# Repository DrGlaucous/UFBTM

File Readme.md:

# UFBTM
~~*Unnamed Full Body Tracking modules*~~

*They have a name now...*
# Mr. Tracker
A cheap, compact, and open-source realtime tracking module built with slimeVR and the ESP32.

<div style="display: flex;">

</div>

## Design goal
<details open>
<summary>
    Details
</summary>

The components for these trackers have been chosen to be **exclusively through-hole** for ease of assembly (at a slight cost of a larger size)

The main IMU this design is based around is the BMI160, primarily for its low cost and small breakout footprint. This IMU is notorious for drifting, so it is also paired with a GY-271 magnetometer to mitigate some of the drift (depending on use location, the magnetometers may need to be disabled due to poor magnetic field).

<figure align = "center">

</figure>

This idea is by no means novel; I'm not even the first person to use the components I'm using, but I'm attempting to take a cost approach here. The full tracking set (10 modules + 5 extenders) can potentially be as low as $100 USD without print time costs or filament prices.

Assembly should be quick and reliable with no need for SMD or rework, which is something other modules of this size can't do.

The module uses TRRS (4 ring) aux jacks to connect between the main board and its extender, providing a robust connection that can last many plug cycles and be easily replaced if the wire goes bad.

Battery life of these trackers should be comparable to official ESP8266-based slime trackers, though I've only personally used them for about 6-8 hours at a time.

</details>

## Compatibility

<details>
<summary>
    MCU
</summary>

### MCU
For the microcontroller, this board can support anything with the "superMini" form factor with the 8 or 9 pin length (including the s3 variants, though I haven't tested the firmware with the s3)

<div class="image-row" style="display:flex;flex-wrap:wrap">
    <div class="image-col" style="flex:50%">
        <div class="grid-item">
            
        </div>
    </div>
    <div class="image-col" style="flex:50%">
        <div class="grid-item">
            
        </div>
    </div>
</div>

> [!NOTE]
> ***Check to make sure the +5v, GND, and +3.3v on the board match the "standard" superMini layout as seen above! Some boards like to mix them around, like the one below. That one WILL NOT WORK.***

<figure align = "center">

<figcaption align = "center"><i>Note how the power pins are on the opposite side from the normal superMini board</i></figcaption>
</figure>

---
My preference is the variant commonly labeled as "Pro Minis" or "C3 Minis" because [the normal "Supermini" modules can have issues with antenna reception](https://peterneufeld.wordpress.com/2025/03/04/esp32-c3-supermini-antenna-modification/), depending on which ones you get. *(and it's a mixed bag, so you're never really sure if you're getting the right ones)*

The "Pro Mini" modules have a larger antenna that seems further spaced from the rest of the components. They're distinct enough that you always know you're getting the right type of board, and as far as I can tell, haven't been complained about online. They also have a place for an external antenna, should you ever want to go that route. SuperMini v2 modules also work well, but are typically more expensive.

<figure align = "center">

<figcaption align = "center"><i>An example of an "ESP32 C3 pro mini"</i></figcaption>
</figure>

</details>

---

<details>
<summary>
    IMU
</summary>

### IMU
The IMU can be anything that matches the BMI160 breakout form-factor.
This includes:
- The BMI160 itself
- The LSM6DS3 (*note: getting these from AliExpress will often just get you a re-badged BMI160.*) These aren't officially supported by the upstream slimeVR firmware as-of-writing, but are supported by my custom fork.
- Slimevr "Mumo" boards hosting a CM-45686 module
- [Mofflab](https://moffshop.deyta.de/products/lsm6dsv-module) LSM6DSV modules *(I'm sure there are other vendors of these that I haven't mentioned, but these are all I could find while searching the internet. Join the SVR discord if you want to find better sources)*

<div class="image-row" style="display:flex;flex-wrap:wrap">
    <div class="image-col" style="flex:50%">
        <div class="grid-item">
            
        </div>
        <div class="grid-item">
            
        </div>
    </div>
    <div class="image-col" style="flex:50%">
        <div class="grid-item">
            
        </div>
        <div class="grid-item">
            
        </div>
    </div>
</div>

</details>

---

<details>
<summary>
    Magnetometer
</summary>

### Magnetometer

The PCB was designed to hold a GY-271 magnetometer breakout board.
These boards are common enough, but tend to have several variants of actual magnetometer on them, including:
- HMC5883L
- QMC5883L
- QMC5883P

All these are supported by my fork of the slimeVR firmware *(with the BMI160 and LSM6DS3, I haven't tested with the mumos or mofflab boards, but if the IMU on those are good enough, you shouldn't need a magnetometer anyway)*, but they have distinct registers, so you will have to check which one you have. (as-of-writing, the QMC5883P is the most common of these)

<figure align = "center">

</figure>

</details>

---

<details>
<summary>
    Charger
</summary>

### Charger

One of the most compact jellybean chargers are the `LX-LBES` chargers. They tend to come in 2 distinct sizes, and it's unreliable which one you might get. The PCB can support either of them though, so this shouldn't be a problem. These are also commonly labeled as `TP4057` charger boards.

Just make sure it's the `LX-LBES` module and not the other variants like the `LX-MILC` or `LX-LBC3`, both of which are similarly sized, but are incompatible.

<figure align = "center">
<div class="image-row" style="display:flex;flex-wrap:wrap">
    <div class="image-col" style="flex:50%">
        <div class="grid-item">
            
        </div>
    </div>
    <div class="image-col" style="flex:50%">
        <div class="grid-item">
            
        </div>
    </div>
</div>
<figcaption align = "center"><i>On the left: the smaller of the two LX-LBES boards, on the right: the more common larger variant. Both of these will work for these trackers</i></figcaption>
</figure>

<figure align = "center">

</figure>

</details>

---

<details>
<summary>
    Battery
</summary>

### Battery

This tracker is designed to work with 2 distinct battery sizes:
- The 804040 (a square flat-pack, used with Mr. Tracker PCBs)
- The 18650 (a common cylindrical battery, used with Mrs. Tracker PCBs)

Unfortunately, I have not modeled a housing for the 18650 variant yet.

18650 batteries are cheaper than the 804040s, especially if you get them used from a place like [batteryhookup](https://batteryhookup.com/), where they cost about 50c per battery. Depending on the quality of the cell, they can also hold more charge than the 804040s, but as a trade-off are inconveniently shaped for trackers. The Mrs. Tracker PCB is designed to accommodate these long, skinny batteries as best as possible.

<figure align = "center">

</figure>

</details>

---

<details>
<summary>
    LDO
</summary>

### LDO

The LDO regulates the incoming battery voltage down to 3.3 volts for the electronics. The board will accept any LDO in a TO-92 package, but was designed around the HT7333 regulator as that is what I could get off Amazon.

If the LDO you select has a different pinout than the HT7333, then you will need to reconfigure the jumpers as described in [Power configuration](#power-configuration).

<figure align = "center">

</figure>

This part is optional if your IMU has a built-in 5v to 3.3v regulator **that can support the currents required by the ESP32 and other componets**. I've seen some that both could and couldn't, so I'd assume the worst case and use a discrete LDO for safety.

The MCP1700 also shares the same pinout and is rated at 250mA.

#### Capacitor requirements
Many of these LDOs require an inline capacitor for voltage smoothing and stable output (for example, the datasheet for the MCP1700 regulator says it requires at least a 1uf capacitor). I was able to find 10uf ceramic capacitors to use in my design, but you may be able to get away with smaller values, or even none at all. The HT7333 worked without a capacitor too, but it would have trouble slightly sooner than with a capacitor when the battery voltage got too low.

</details>

## Bill of Materials

Prices are generally cheaper if you buy in bulk from China, which is recommended since you'll likely be building at least five of these and need to order the PCBs from there anyway. (unless you *have* to use a domestic PCB manufacturer, in which case you'll probably end up paying several times more than ordering through a provider like JLCPCB)
Most of this stuff should be available to get on Amazon as well, albeit more expensive.

I've added some links to the BOMs below to help new builders get started, but there might be better deals for the same parts with some shopping around, which I encourage you to do.

> [!NOTE]
> ***Some of the links below have multiple options on the listing (like the resistors for instance. Make sure you choose the correct type!)***

### Mr/Mrs. Tracker part list
---
|part|qty per tracker|qty per package (typical)|price per package (typical, USD)|Link (non-affiliate, U.S. domain, may be expired)|
|-|-|-|-|-|
|PCB (ordered from PCB provider)|1|5-20|~$10 excluding shipping|[JLCPCB](https://jlcpcb.com/)|
|ESP32 C3 [(see compatible devices)](#mcu)|1|1|~$2.5|[AliExpress](https://www.aliexpress.us/item/3256808596276264.html)
|IMU [(see compatible devices)](#imu)|1|1|~$2.5|[AliExpress](https://www.aliexpress.us/item/3256806936640318.html)
|GY-271 Magnetometer [(see compatible devices)](#magnetometer) *(optional, but recommended to limit drift)*|1|1|~$2|[AliExpress](https://www.aliexpress.us/item/3256808812894856.html)
|LX-LBES li-ion charger [(see compatible devices)](#charger)|1|5-10|~$5|[AliExpress](https://www.aliexpress.us/item/3256807364882965.html)
|3.3v LDO [(see compatible devices)](#ldo)|1|20-100|~$3|[AliExpress](https://www.aliexpress.us/item/3256807332164741.html)
|10uF Ceramic Capacitor [(maybe optional, see LDO)](#capacitor-requirements)|1|100|~$3|[AliExpress](https://www.aliexpress.us/item/3256809085304078.html)
|200K resistor (for voltmeter)|2|100|~$2|[AliExpress](https://www.aliexpress.us/item/3256802310109990.html)
|On-Off Switch (SK12D07VG4)|1|100|~$2|[AliExpress](https://www.aliexpress.us/item/2251832696379644.html)
|TRRS Connector (PJ-320A) *(Optional, for extenders)*|1|20|~$2|[AliExpress](https://www.aliexpress.us/item/2255800974971563.html)
|M2.5x6 self tapping screws|5|50|~$2|[AliExpress](https://www.aliexpress.us/item/3256805374708201.html), [Amazon](https://a.co/d/0iR6Q6Wc)
|804040 battery|1|5|~$18 USD|[AliExpress](https://www.aliexpress.us/item/3256806179780660.html)
|Elastic straps, 25mm wide|Varies|5 Meters|~$4|[AliExpress](https://www.aliexpress.us/item/2251832835409359.html)
|Strap Buckles, 25mm wide|1|5|~$5|[AliExpress](https://www.aliexpress.us/item/3256805860301514.html)
|Sewing thread for attaching buckles to straps|Varies|Varies|N.A.|N.A.
|Plastic housing|1|N.A.|N.A.|N.A.

### Extender (Tracker Jr) part list
---

|part|qty per tracker|qty per package (typical)|price per package (typical, USD)|Link (non-affiliate, U.S. domain, may be expired)|
|-|-|-|-|-|
|PCB (ordered from PCB provider)|1|5-20|~$10 excluding shipping|[JLCPCB](https://jlcpcb.com/)|
|IMU [(see compatible devices)](#imu)|1|1|~$2.5|[AliExpress](https://www.aliexpress.us/item/3256806936640318.html)
|GY-271 Magnetometer [(see compatible devices)](#magnetometer) *(optional, but recommended to limit drift)*|1|1|~$2|[AliExpress](https://www.aliexpress.us/item/3256808812894856.html)
|TRRS Connector (PJ-320A)|1|20|$2|[AliExpress](https://www.aliexpress.us/item/2255800974971563.html)
|TRRS Male-Male Aux cable, 1 meter|1|1|$2|[AliExpress](https://www.aliexpress.us/item/3256805991501373.html)
|Elastic straps, 25mm wide|Varies|5 Meters|$4|[AliExpress](https://www.aliexpress.us/item/2251832835409359.html)
|Strap Buckles, 25mm wide|1|5|~$5|[AliExpress](https://www.aliexpress.us/item/3256805860301514.html)
|Sewing thread for attaching buckles to straps|Varies|Varies|N.A.|N.A.
|Plastic housing|1|N.A.|N.A.|N.A.

## Power configuration

<details>
<summary>
    Details
</summary>

Rev. 3 boards have several jumpers on the underside that changes how the device can be powered so a wider range of parts can be used.

Depending on the quality of the IMU breakout board, the linear regulator and voltage smoothing capacitor may not be needed. This varies more than you'd think with distributors though, so it's not always safe to count on it. Additionally, some versions of the IMU breakout might not even have an integrated regulator at all, making the discrete regulator required.

- Jumpers `A`, `B`, `C`, and `D` alter the pinout for the voltage regulator and allow one with any pin arrangement to be installed.
- Connecting jumper `E` allows the board to use the voltage regulator on the IMU instead of the discrete one.
- Connecting jumper `F` allows the ESP32's USB port to charge the battery. The drawback is that charging the tracker will *always* turn on the ESP32, wasting power and charging slower.

The following is a table of all the possible voltage regulator pinouts and their corresponding jumper configs. An "O" means to leave the jumper at default (bridging positions 1 and 2), an "X" means to cut the jumper and flip it (bridging positions 2 and 3). "Flip" means to solder the regulator into the socket backwards 

>[!NOTE]
> Although I tried to keep the ABCD jumpers next to each other, their orientations are flipped! Pay close mind to what side of the jumper pad the "1" and "3" are on in the silkscreen!

|Pinout|A|B|C|D|Flip|
|-|-|-|-|-|-|
||O|O|O|O|O|
||O|O|X|X|O|
||X|X|O|O|O|
||X|X|O|O|X|
||O|O|X|X|X|
||O|O|O|O|X|

In a nutshell,
- AB flip 1 and 2,
- CD flip 2 and 3

</details>

---

> [!CAUTION]
> Everything below this point is very unfinished (as opposed to only slightly unfinished, as is seen above)

## Ordering PCBs

todo: this

## Recommended tools for assembly

In theory, these trackers can be assembled just fine with a [Wal-Mart special](https://www.walmart.com/ip/EverStart-Soldering-Iron-Model-5133-Red-120V-30W-Automotive-Electrical-Tool-New/744820237) *(link included for meme purposes only!)* soldering iron, a pair of children's safety scissors, a manicure file, and a sewing needle. Will you have a good time doing it? No, but it's definitely possible.

Instead of that, here's the list of tools I recommend to make assembly of these go smoothly:

- A Soldering Iron (the Wal-Mart special will work, but I suggest getting something at least partway decent on Amazon; good soldering irons can be had for less than $30.)
- Solder (lead solder is easier to work with, but lead-free works OK too if you're cautious about working with lead.)
- Flush cutters
- A needle file set (optional)
- SMD Tweezers
- Helping hands vice (optional)
- Small phillips screwdriver (for the screws on the housing)

For the straps:
- A pair of scissors (preferably not child safety ones)
- A lighter
- A sewing needle or sewing machine
- Sewing thread

## Assembly Preface

These guides assume you have everything in hand required to build one of these trackers.

Typically, a good rule of thumb is to start with the lowest profile components first and work your way up by height. Most of the stuff on these trackers is the same height however, so order isn't ultra-important; nothing really gets in the way of anything else, but regardless, I still like to start with the breakout boards *(MCU, IMU, Magnetometer, and Charger)*.

To keep the tracker as compact as possible, the breakouts are soldered directly on top of the board. This makes them much more difficult to remove though, so be careful during assembly!

I've had an IMU come to me dead on arrival and had to go through the painstaking process of desoldering it from the board. (which involved simultaneously heating the pins and wedging an xacto between the IMU and the PCB)
Because of that, I like to make sure that parts work beforehand by soldering up a test rig with removable pins to test parts with.

Working with a breadboard for testing is feasible too, but it's less likely that people would just have one of those onhand, much less the desire to wire an entire setup just to see if a few parts maybe don't work.

## Assembly (Mr. Tracker)

<details>
<summary>
    Details
</summary>

</details>

## Assembly (Mrs. Tracker)

## Assembly (Tracker Jr)

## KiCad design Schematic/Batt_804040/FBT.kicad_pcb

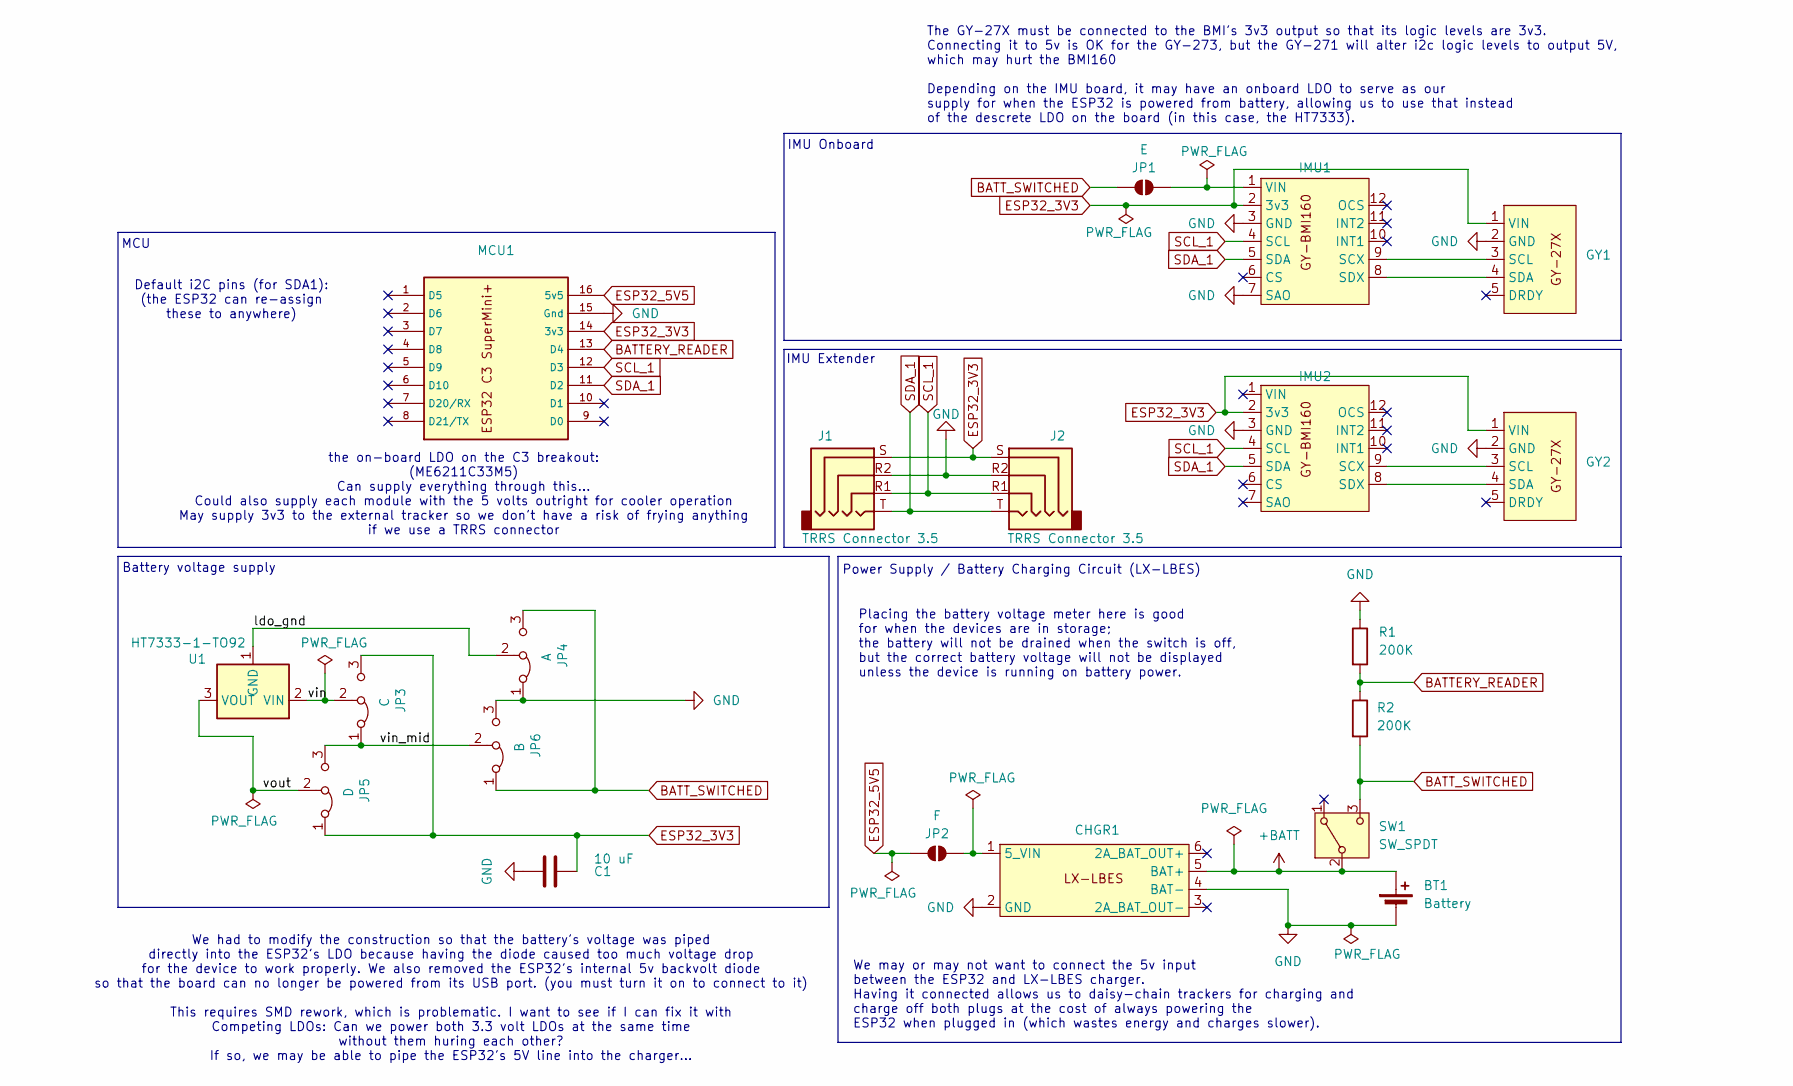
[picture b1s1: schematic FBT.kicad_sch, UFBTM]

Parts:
BT1: Battery; JST_XH_B2B-XH-A_1x02_P2.50mm_Vertical
C1: 10 uF; C_Disc_D5.0mm_W2.5mm_P5.00mm
CHGR1: LX_LBES
GY1, GY2: GY-271
IMU1, IMU2: GY-BMI160
J1, J2: TRRS Connector 3.5; PJ-320A
JP1: E; SolderJumper-2_P1.3mm_Open_RoundedPad1.0x1.5mm
JP2: F; SolderJumper-2_P1.3mm_Open_RoundedPad1.0x1.5mm
JP3: C; SolderJumper-3_P1.3mm_Bridged12_RoundedPad1.0x1.5mm_NumberL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
JP4: A; SolderJumper-3_P1.3mm_Bridged12_RoundedPad1.0x1.5mm_NumberL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
JP5: D; SolderJumper-3_P1.3mm_Bridged12_RoundedPad1.0x1.5mm_NumberL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
JP6: B; SolderJumper-3_P1.3mm_Bridged12_RoundedPad1.0x1.5mm_NumberL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
MCU1: ESP32-C3-SuperMini_PLUS
R1, R2: 200K; R_Axial_DIN0207_L6.3mm_D2.5mm_P7.62mm_Horizontal
SW1: SW_SPDT; SK12D07VG4
U1: HT7333-1-TO92; TO-92L_Inline

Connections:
+BATT: BT1.1 (+), CHGR1.5 (BAT+), SW1.2 (B); also elsewhere on the board
/ldo_gnd: JP4.2 (C), U1.1 (GND)
/vin: JP3.2 (C), U1.2 (VIN)
/vin_mid: JP3.1 (A), JP5.3 (B), JP6.2 (C)
/vout: JP5.2 (C), U1.3 (VOUT)
BATTERY_READER: MCU1.13 (D4), R1.2, R2.1
BATT_SWITCHED: JP1.2 (B), JP4.3 (B), JP6.1 (A), R2.2, SW1.3 (C)
ESP32_3V3: C1.1, GY1.1 (VIN), GY2.1 (VIN), IMU1.2 (3v3), IMU2.2 (3v3), J1.S, J2.S, JP3.3 (B), JP5.1 (A), MCU1.14 (3v3)
ESP32_5V5: JP2.2 (B), MCU1.16 (5v5)
GND: BT1.2 (-), C1.2, CHGR1.2 (GND), CHGR1.4 (BAT-), GY1.2 (GND), GY2.2 (GND), IMU1.3 (GND), IMU1.7 (SAO), IMU2.3 (GND), J1.R2, J2.R2, JP4.1 (A), JP6.3 (B), MCU1.15 (Gnd), R1.1; also elsewhere on the board
unnamed 10: CHGR1.1 (5_VIN), JP2.1 (A); also elsewhere on the board
unnamed: GY1.3 (SCL), IMU1.9 (SCX)
unnamed: GY1.4 (SDA), IMU1.8 (SDX)
unnamed: GY2.3 (SCL), IMU2.9 (SCX)
unnamed: GY2.4 (SDA), IMU2.8 (SDX)
unnamed: IMU1.1 (VIN), JP1.1 (A)
SCL_1: IMU1.4 (SCL), IMU2.4 (SCL), J1.R1, J2.R1, MCU1.12 (D3)
SDA_1: IMU1.5 (SDA), IMU2.5 (SDA), J1.T, J2.T, MCU1.11 (D2)

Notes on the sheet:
We may or may not want to connect the 5v input between the ESP32 and LX-LBES charger. Having it connected allows us to daisy-chain trackers for charging and charge off both plugs at the cost of always powering the ESP32 when plugged in (which wastes energy and charges slower).
IMU Extender
MCU
We had to modify the construction so that the battery's voltage was piped directly into the ESP32's LDO because having the diode caused too much voltage drop for the device to work properly. We also removed the ESP32's internal 5v backvolt diode so that the board can no longer be powered from its U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
Power Supply / Battery Charging Circuit (LX-LBES)
IMU Onboard
Placing the battery voltage meter here is good for when the devices are in storage; the battery will not be drained when the switch is off, but the correct battery voltage will not be displayed unless the device is running on battery power.
the on-board LDO on the C3 breakout: (ME6211C33M5) Can supply everything through this... Could also supply each module with the 5 volts outright for cooler operation May supply 3v3 to the external tracker so we don't have a risk of frying anything if we use a TRRS connector
Battery voltage supply
The GY-27X must be connected to the BMI's 3v3 output so that its logic levels are 3v3. Connecting it to 5v is OK for the GY-273, but the GY-271 will alter i2c logic levels to output 5V, which may hurt the BMI160 Depending on the IMU board, it may have an onboard LDO to serve as our supply for when 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
Default i2C pins (for SDA1): (the ESP32 can re-assign these to anywhere)

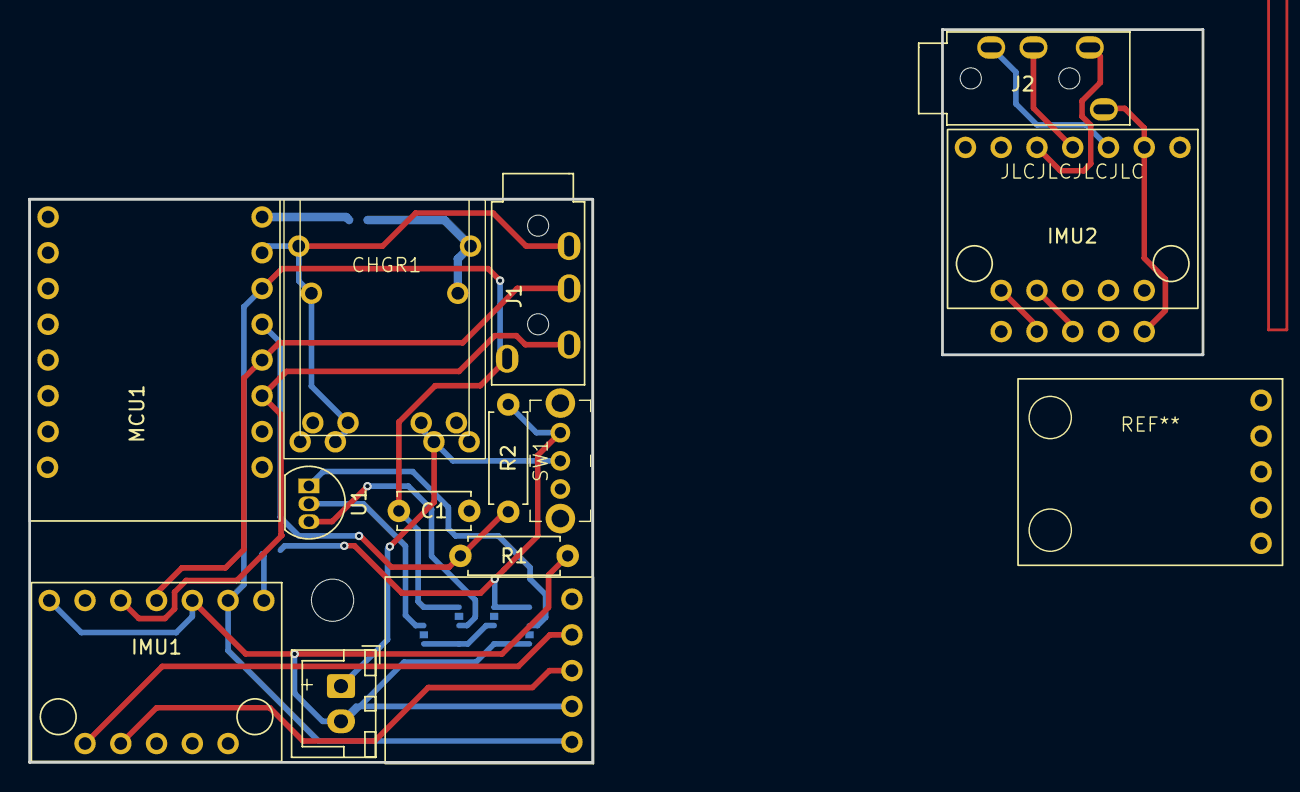
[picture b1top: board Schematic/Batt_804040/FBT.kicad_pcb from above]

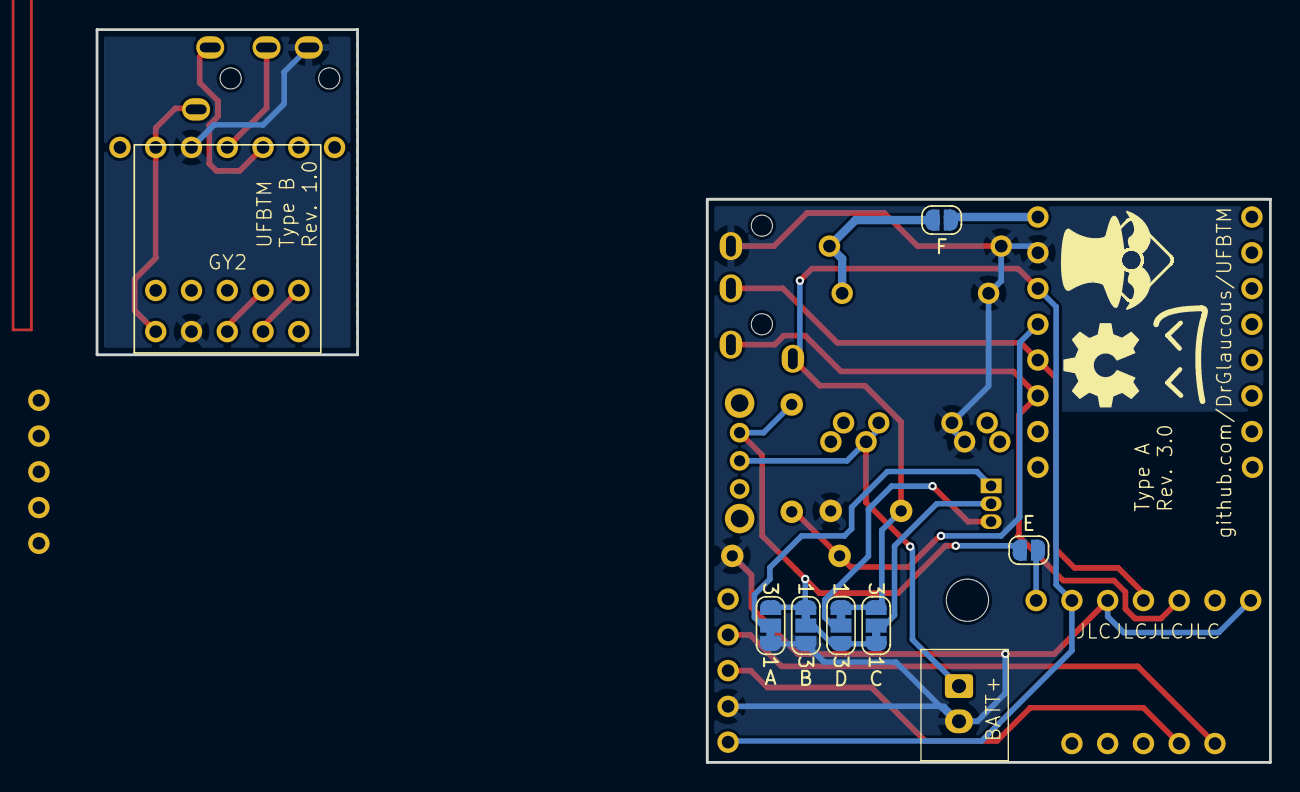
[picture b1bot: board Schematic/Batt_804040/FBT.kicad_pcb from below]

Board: 2 copper layers, 40.0 x 40.0 mm, 21 parts (7 on the bottom side), 18 nets.

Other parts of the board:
CHGR2: LX-LBES-Big

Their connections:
+BATT: CHGR2.5 (BAT+); also elsewhere on the board
GND: CHGR2.2 (GND), CHGR2.4 (BAT-); also elsewhere on the board
unnamed 10: CHGR2.1 (5_VIN); also elsewhere on the board

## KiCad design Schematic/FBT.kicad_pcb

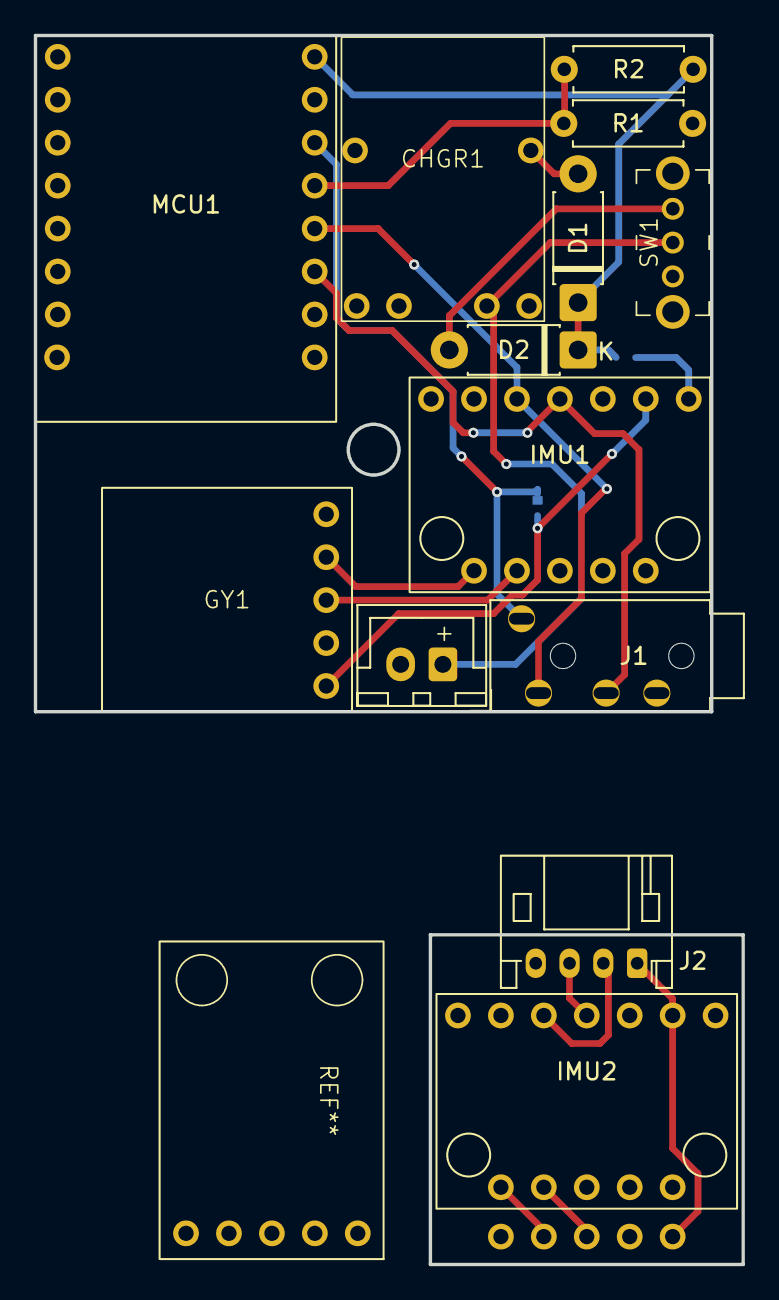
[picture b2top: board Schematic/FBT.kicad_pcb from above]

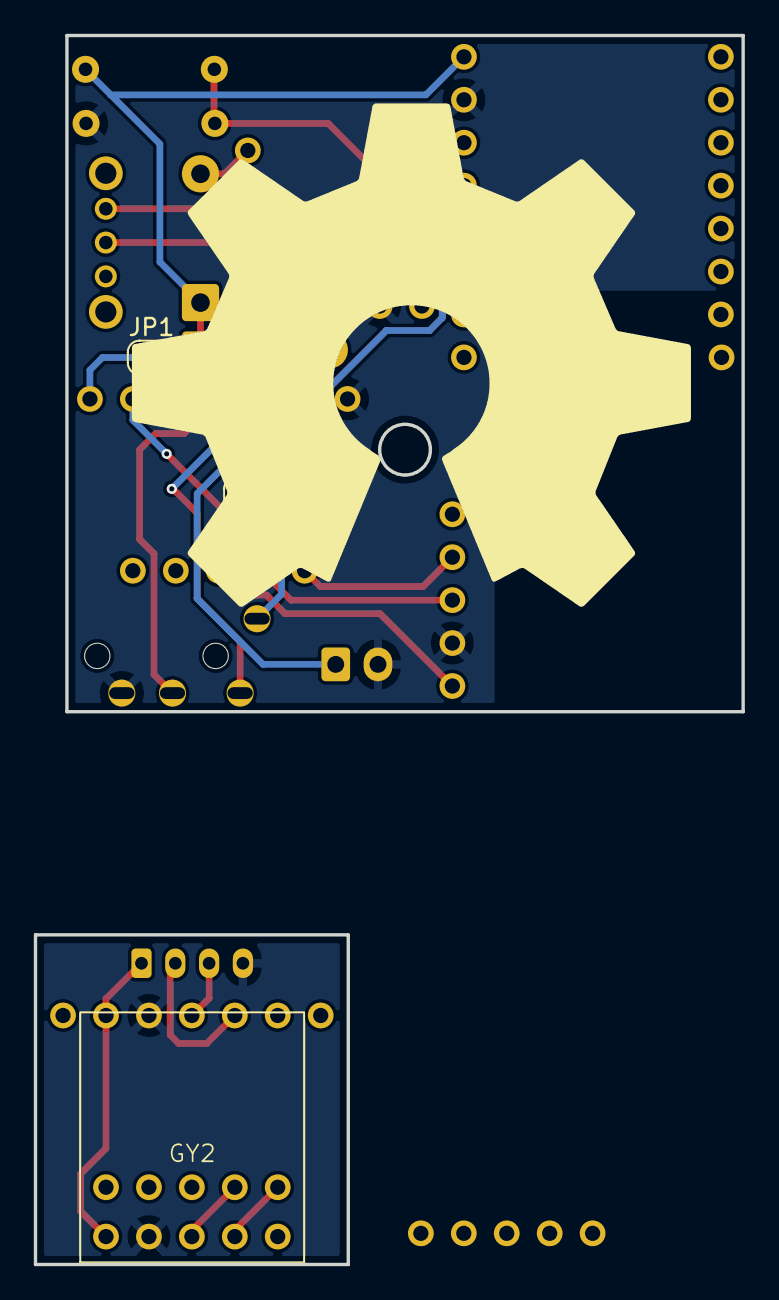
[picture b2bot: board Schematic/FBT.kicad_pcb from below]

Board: 2 copper layers, 41.9 x 72.7 mm, 16 parts (3 on the bottom side), 15 nets.

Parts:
BT1: Battery; JST_XH_B2B-XH-A_1x02_P2.50mm_Vertical
CHGR1: LX_LBES
D1: D_1N5817 / 4.8v Zener?; D_DO-41_SOD81_P7.62mm_Horizontal
D2: D_1N5817; D_DO-41_SOD81_P7.62mm_Horizontal
GY1, GY2: GY-271
IMU1, IMU2: GY-BMI160
J1: TRRS Connector 3.5; PJ-320A
J2: Conn_01x04; JST_PH_S4B-PH-K_1x04_P2.00mm_Horizontal
JP1: 5v in; SolderJumper-2_P1.3mm_Open_RoundedPad1.0x1.5mm
JP2: 3v3 in; SolderJumper-2_P1.3mm_Bridged_RoundedPad1.0x1.5mm
MCU1: ESP32-C3-SuperMini_PLUS
R1, R2: 200K; R_Axial_DIN0207_L6.3mm_D2.5mm_P7.62mm_Horizontal
SW1: SW_SPDT; SK12D07VG4

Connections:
+BATT: BT1.1 (+), CHGR1.5 (BAT+), SW1.2 (B)
BATTERY_READER: MCU1.13 (D4), R1.2, R2.1
ESP32_3V3: GY2.1 (VIN), IMU2.2 (3v3), J1.T, J2.1, JP2.1 (A), MCU1.14 (3v3)
ESP32_5V5: D1.1 (K), D2.1 (K), JP1.2 (B), MCU1.16 (5v5), R2.2
GND: BT1.2 (-), CHGR1.2 (GND), CHGR1.4 (BAT-), GY1.2 (GND), GY2.2 (GND), IMU1.3 (GND), IMU1.7 (SAO), IMU2.3 (GND), J1.S, J2.4, MCU1.15 (Gnd), R1.1
unnamed: CHGR1.1 (5_VIN), D1.2 (A)
unnamed: D2.2 (A), SW1.3 (C)
unnamed: GY1.3 (SCL), IMU1.9 (SCX)
unnamed: GY1.4 (SDA), IMU1.8 (SDX)
unnamed: GY1.1 (VIN), IMU1.2 (3v3), JP2.2 (B)
unnamed: GY2.3 (SCL), IMU2.9 (SCX)
unnamed: GY2.4 (SDA), IMU2.8 (SDX)
unnamed: IMU1.1 (VIN), JP1.1 (A)
SCL_1: IMU1.4 (SCL), IMU2.4 (SCL), J1.R2, J2.3, MCU1.11 (D2)
SDA_1: IMU1.5 (SDA), IMU2.5 (SDA), J1.R1, J2.2, MCU1.12 (D3)

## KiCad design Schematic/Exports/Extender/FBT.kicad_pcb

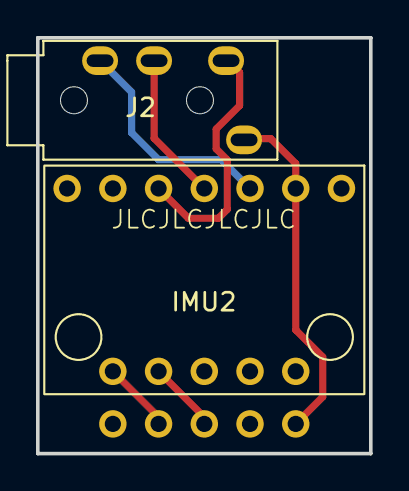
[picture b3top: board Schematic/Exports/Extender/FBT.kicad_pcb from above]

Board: 2 copper layers, 18.5 x 23.1 mm, 3 parts (1 on the bottom side), 6 nets.

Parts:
GY2: GY-271
IMU2: GY-BMI160
J2: TRRS Connector 3.5; PJ-320A

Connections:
ESP32_3V3: GY2.1 (VIN), IMU2.2 (3v3), J2.T
GND: GY2.2 (GND), IMU2.3 (GND), J2.S
unnamed: GY2.3 (SCL), IMU2.9 (SCX)
unnamed: GY2.4 (SDA), IMU2.8 (SDX)
SCL_1: IMU2.4 (SCL), J2.R2
SDA_1: IMU2.5 (SDA), J2.R1

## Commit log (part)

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2025-06-10 Add references and work on schematic
2025-06-10 More schematic work
    I'm kind of hung up on what charging circuit to use...
2025-06-16 work on PCB and shell
2025-06-19 Add firmware from SVR
    unmodified
2025-06-21 Switch to SVR firmware 0.5.2
    0.6.0 has some problems with my MCU (crash-on-startup)
2025-06-21 more tweaks and changes
2025-06-21 Work on housing
2025-06-22 create driver for QMC5883P
    Amazon scammed me
    Todo next: integrate this into the SVR firmware
2025-06-22 Magnetometer now interfaces with the IMU
    Still doesn't show up in SVR server for some reason...
2025-06-22 clean up sensor implementation
2025-06-23 Bump firmware version to 0.5.4
    Tried 0.6.0, but that crashes on the esp32-C3.
    0.5.4 is the latest stable release though, so I'll go with that for now.
2025-06-23 Bring over changes from the 0.5.2 firmware
    Don't quite know why 0.5.4 broke the first time, but it works now.
2025-06-23 Re-work PCB and add more IMU refs
    Trying to make this as dynamic as possible
2025-06-25 Measurements, notes, tweaks
    Finding and fixing problems as I get ready to order parts for these
2025-06-25 schematic work and notes
2025-06-26 work on shell, add notes
2025-06-26 split schematic and mark firmware
    Planning to make 2 types of PCB layouts for different kinds of batteries.
    Also marked points in the firmware that are of particular interest to me (getting/sending magnetometer status to the frontend)
2025-06-30 Work on silkscreen logo
    Made a mascot, "Mr. Tracker" which looks a lot like Mr. Lunt mixed with Pa Grape.
2025-07-01 Work on shell and PCB
    Needed to do more work on the extended tracker
2025-07-02 work on PCBs, logos, and case
    did more work on 18650 battery model
2025-07-08 Work on 18650 PCB
    It's done, but I may re-do this one to flip the ESP32 sideways...
    (I then proceeded to work on the sideways version)
2025-07-08 straggling files
    why weren't these committed with the others?
2025-07-09 Final touches for fabrication
    Sent designs off to JLBPCB... hopefully they work...
2025-07-11 Rework MrTracker footprint to support the big lx-lbes
2025-07-11 work on correcting Ms. Tracker
    it has to be a little bit bigger unfortunately...
2025-07-11 straggling commit
2025-07-15 prep v2 PCB for production
2025-07-17 Bugfix QMC5883P and work on LSM6DS3 support
    I forgot to map the QMP data to the output. oops.
2025-08-05 PCB updates and some firmware testing
    Also begin finalizing the 3d model for the tracker case.
    I've decided to flip it upside down.
2025-08-07 Working more on shell
    flipped it upside down essentially
2025-08-08 Finished basic big shell
    time to work on the extenders
2025-08-11 More CAD work
    printing tests and resizing
2025-08-13 More size fitting
2025-08-26 Undo flip transform and debug magnetometer
    Turns out the flip transform can already be done with axis remaps. This solves some other problems I've been having as well.
    I'm still struggling to get magnetometer orientation correct though.
2025-08-26 Add test framework for checking magnetometer flux
    prefixed all unneeded modifications with //test:
2025-08-26 Add nearly exhaustive list of remaps to try
    I feel like I could do this a better way, but oh well... I guess it gets the job done
    I'm not smart enough for better methods currently
2025-08-27 some slight work on LSM6ds3 sensor
    mainly adding annotations
2025-08-28 Try modifying lsm6ds3trc for lsm6ds3
    Todo: fully integrate it into the list
2025-09-05 Axis remapping for main IMUs and extenders
    Lots of debug comments and support for live remapping.
    Also some basic implementation stuff for the lsm6ds3 as well (though I think the complete implementation is on my other computer)
2025-09-06 add ability to enable and disable mag for BMI160
    Todo: send magnetometer vector to the computer. The program lists this packet type as deprecated, so I don't know if this is possible.
    The desktop app seems to have support to display it, but there's nothing in the core to take data from the tracker and throw it out in a format the frontend likes.
    also moved old lsm6ds3 implementation to backups since the sensor fusion one should work and I don't have one to test with.
2026-01-05 Move unused firmwares into subfolder
2026-01-17 Start editing schematic for better power supply
    removed diodes and experimenting with multiple LDOs for supplying power from all inputs
2026-02-07 more lsm6ds3 testing
    brought in STM reference to see how they set up secondary sensors
2026-02-07 Got magnetometer reading working
    can now read a QMC5883P from out of an LSM6DS3
    up next is making it work with slimeVR
2026-02-09 add magnetometer interface to sensorFusion
    todo: magnetometer calibration and code format compliance for the LSM6DS3.
    (also re-added axis remapping to the main code)
2026-02-10 Got the LSM6DS3 working correctly with magnetometer
    I need to put this into the upstream firmware.
    I also need to add the proper enable / disable functions to the preprocessor config. I'm currently mooching off of the BMI160 stuff.
2026-02-10 Add better documentation
    It's still not good, but something is better than nothing.
2026-03-18 Update schematic to v3
    Added support for a discrete LDO (HT7333) so we can correct the bodge we did with the original design.
2026-03-23 Slight PCB tweaking
    Double-checking that everything is correct before I ship off the next batch for fabbing.
    Added a jumper pad between usb-c 5v inputs.
2026-06-11 Export the next revision of PCBs for fabrication
    Made at JLCPCB
    Also picked apart the LSM6DS3 datasheet some more. Apparently, the auto hard/soft iron compensation isn't dynamic. It depends on pre-calculated matrices fed into the IMU's registers.
